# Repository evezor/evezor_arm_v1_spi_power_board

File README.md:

# evezor_arm_v1_spi_power_board

This board is inteded to be used with the evezor_arm_v1_mainboard_V1 https://github.com/evezor/evezor_arm_v1_mainboard_V1

It adds a power input for all 5V needs, it adds an sd card and associated ciruitry and an rj45 port that connects to the arm nano board

Source files can be found here: https://github.com/evezor/evezor_arm_v1_spi_power_board

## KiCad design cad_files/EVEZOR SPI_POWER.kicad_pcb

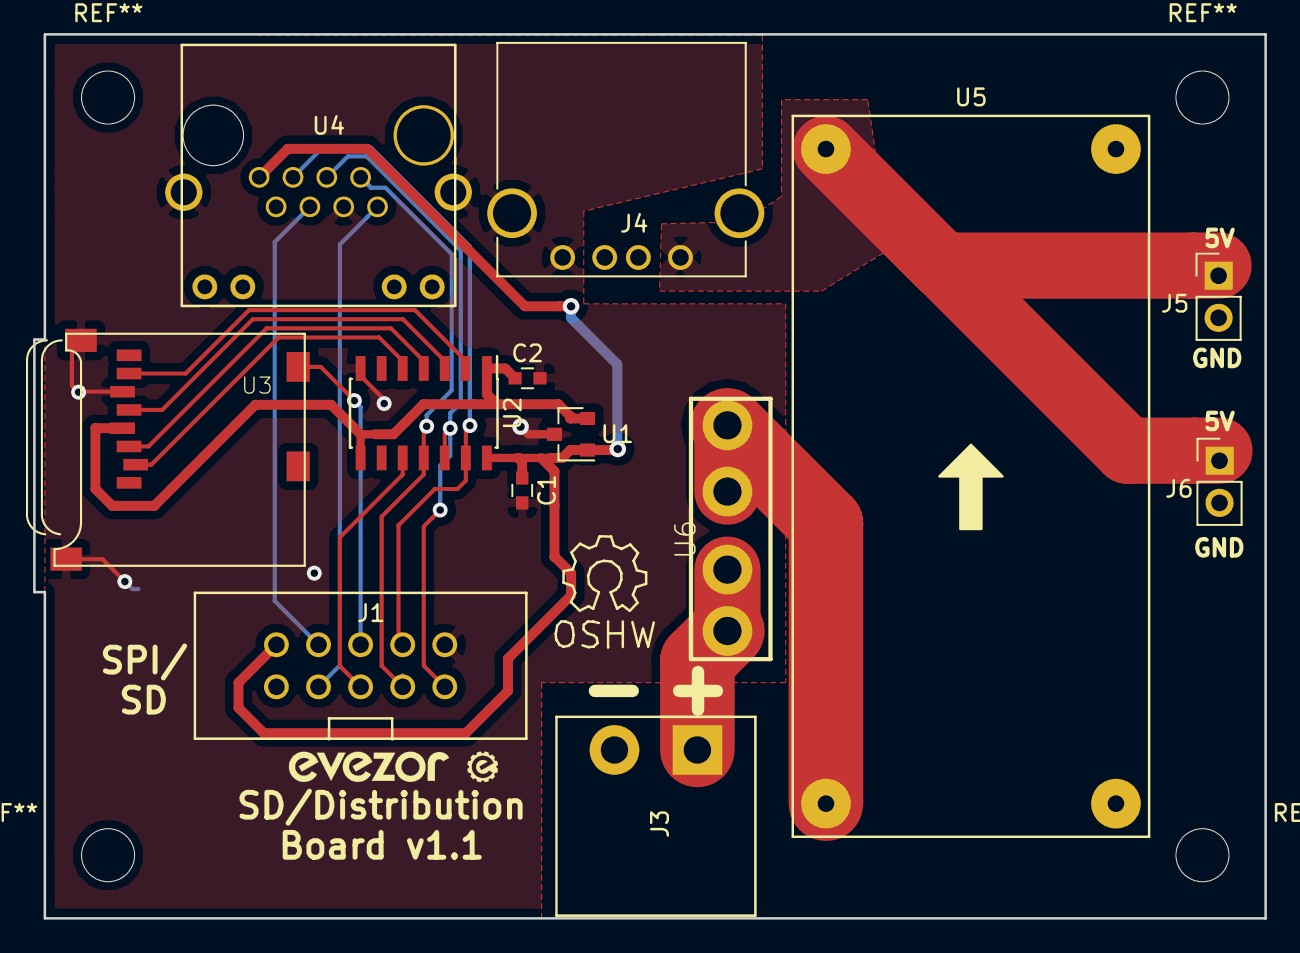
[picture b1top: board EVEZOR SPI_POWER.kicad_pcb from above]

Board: 2 copper layers, 74.3 x 53.3 mm, 13 parts (0 on the bottom side), 17 nets.

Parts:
C1: .1uF; C_0603
C2: 10uF; C_0603
J1: Conn_02x05_Odd_Even; 10_PIN_IDC
J3: Conn_01x02; CONN_ON_SHORE_2x_15A
J4: USB_A
J5, J6: Conn_01x02; Pin_Header_Straight_1x02_Pitch2.54mm
U1: AP7313-33SAG-7DICT-ND; SOT-23
U2: TXB0104D; SOIC-14_3.9x8.7mm_Pitch1.27mm
U3: MICRO_SD; MICROSD
U4: RJ45_SHIELDED_LEDS; RJ45_SHIELDED
U5: VARIABLE_REGULATOR; LM2596_DC-DC
U6: FUSE_AUTO_SMALL; FUSE_BK-6013-ND

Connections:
+3V3: C2.1, U1.2, U2.1, U2.8, U3.4
+5V: C1.1, J1.2, U1.1, U2.14, U4.1
/24V: U5.1, U6.3, U6.4
D32: J1.3, U4.8
D47: J1.4, U4.6
D49: J1.6, U3.CD1
D53: J1.5, U2.10
GND: C1.2, C2.2, J1.10, J3.1, J4.4, J4.5, J5.2, J6.2, U1.3, U2.7, U3.6, U3.MT1, U3.MT2, U4.7, U4.13, U5.2, U5.3
MISO: J1.8, U2.13, U4.2
MOSI: J1.7, U2.11, U4.4
unnamed: J3.2, U6.1, U6.2
unnamed: U2.2, U3.7
unnamed: U2.3, U3.5
unnamed: U2.4, U3.3
unnamed: U2.5, U3.2
RAS_PWR: J4.1, J5.1, J6.1, U5.4
SCK: J1.9, U2.12, U4.3

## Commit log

2023-10-06 init
